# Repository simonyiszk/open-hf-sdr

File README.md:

Open HF SDR
===========

# Specs
* 0.5-30 MHz input freq range

# Receiver
## First stage
* 30 MHz low-pass filter
* Programmable auttenator with 10, 20, and 30 dB options
* Highly linear mixer to 37.224 MHz IF

## Second stage
* IF filter for 37.224 MHz
* IF amplifier
* Mixer to 9 MHz IF

## Third stage
* IF filter for 9 MHz IF with 0.5 MHz bandwidth
* Diff amp to ADC

## Fourth stage
* ADC with 8 MSps, undersampling the 9 MHz IF to 1 MHz

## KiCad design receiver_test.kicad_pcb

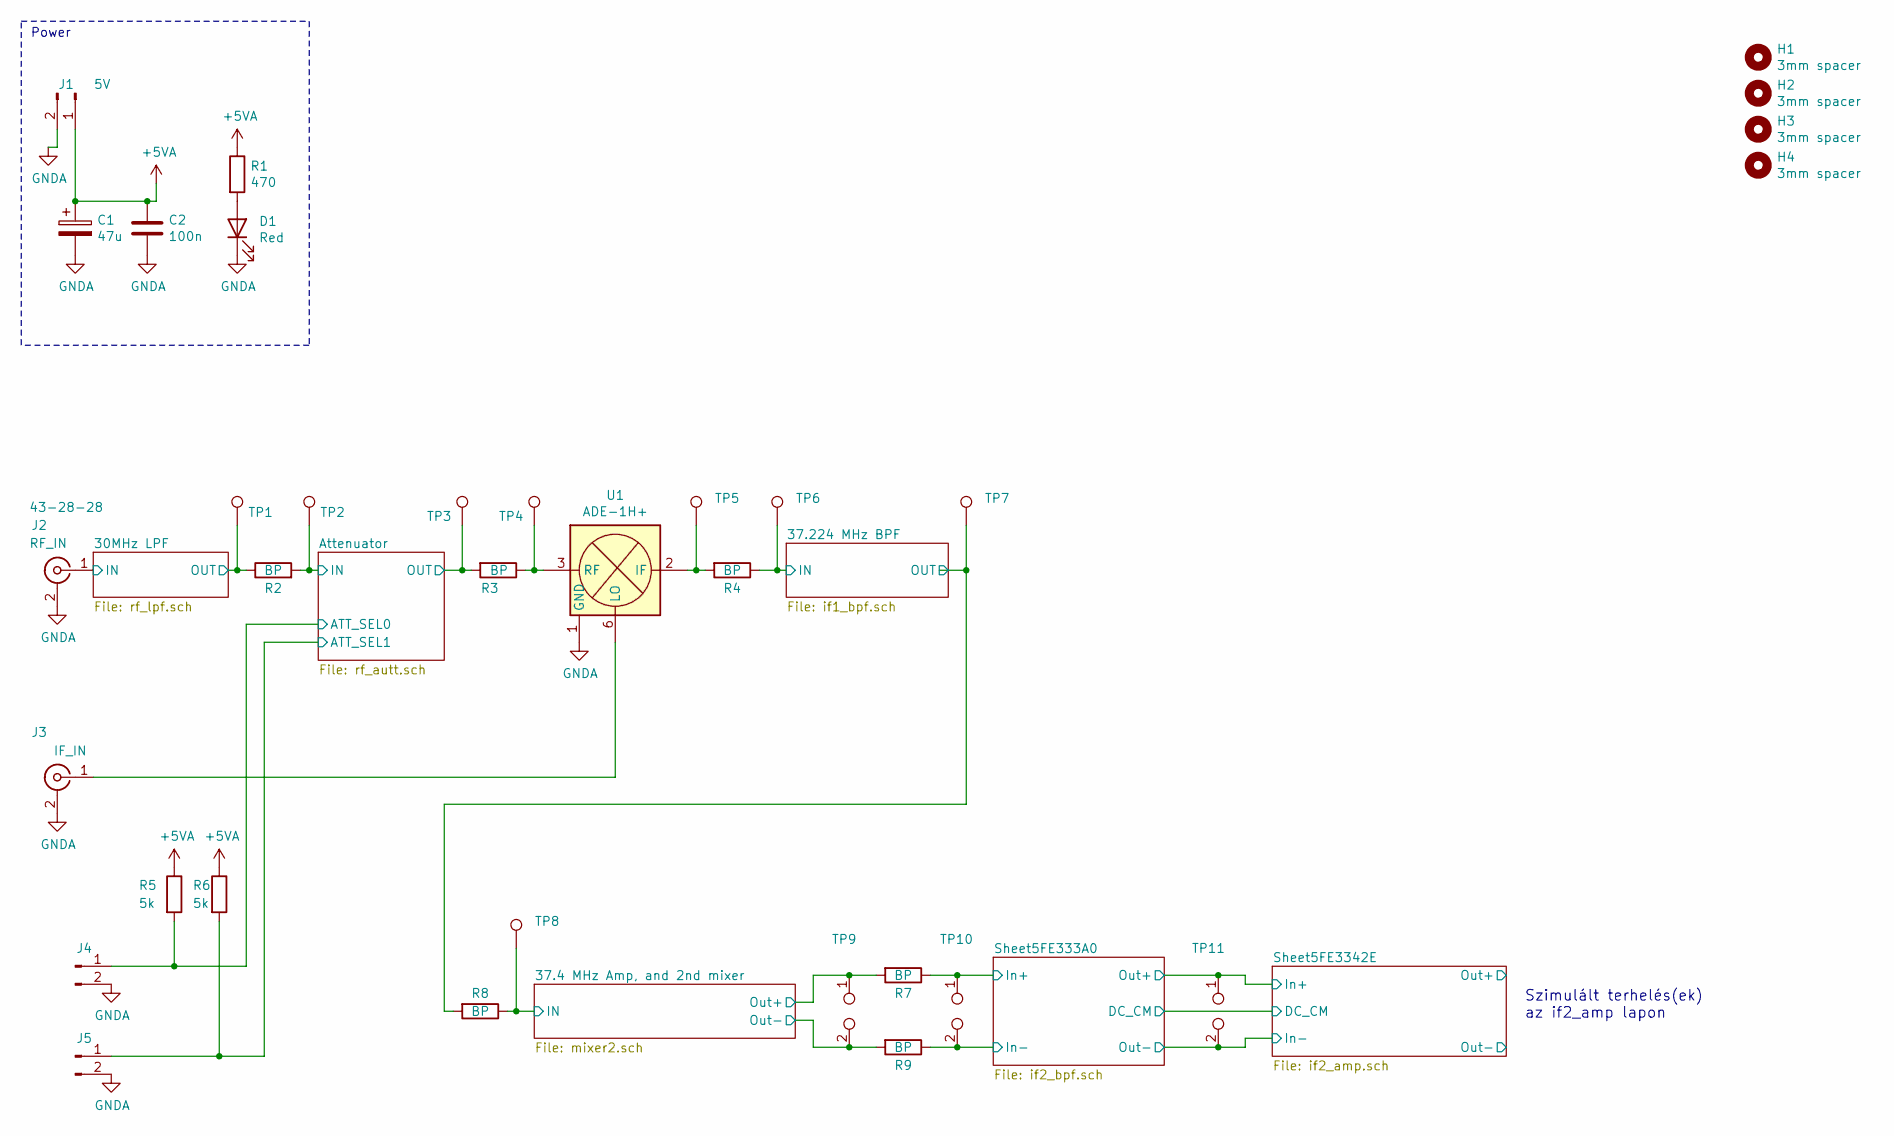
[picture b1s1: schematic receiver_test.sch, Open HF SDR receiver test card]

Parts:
C1: 47u; CP_Elec_6.3x5.3
C2: 100n; C_0805_2012Metric_Pad1.15x1.40mm_HandSolder
D1: Red; LED_0805_2012Metric_Pad1.15x1.40mm_HandSolder
H1, H2, H3, H4: 3mm spacer; MountingHole_3.2mm_M3
J1: 5V; PinSocket_1x02_P2.54mm_Vertical
J2: RF_IN; SMA_Molex_73251-1153_EdgeMount_Horizontal
J3: IF_IN; SMA_Molex_73251-1153_EdgeMount_Horizontal
J4, J5: Conn_01x02_Male; PinSocket_1x02_P2.54mm_Vertical
R1: 470; R_0805_2012Metric_Pad1.15x1.40mm_HandSolder
R2, R3, R4, R7, R8, R9: BP; R_1206_3216Metric_Pad1.42x1.75mm_HandSolder
R5, R6: 5k; R_0805_2012Metric_Pad1.15x1.40mm_HandSolder
TP1, TP2, TP3, TP4, TP5, TP6, TP7, TP8: TestPoint; PinHeader_1x01_P2.54mm_Vertical
TP9, TP10, TP11: TestPoint_2Pole; PinHeader_1x02_P2.54mm_Vertical
U1: ADE-1H+; Mini-Circuits_CD542_LandPatternPL-052

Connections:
+5VA: C1.1, C2.1, J1.1, R1.1, R5.1, R6.1; also elsewhere on the board
/30MHz LPF/IN: J2.1 (In); also elsewhere on the board
/30MHz LPF/OUT: R2.1, TP1.1; also elsewhere on the board
/37.4 MHz Amp, and 2nd mixer/IN: R8.1, TP8.1; also elsewhere on the board
/37.4 MHz Amp, and 2nd mixer/Out+: R7.2, TP9.1; also elsewhere on the board
/37.4 MHz Amp, and 2nd mixer/Out-: R9.2, TP9.2; also elsewhere on the board
/37.224 MHz BPF/IN: R4.1, TP6.1; also elsewhere on the board
/Attenuator/ATT_SEL0: J4.1, R5.2; also elsewhere on the board
/Attenuator/ATT_SEL1: J5.1, R6.2; also elsewhere on the board
/Attenuator/IN: R2.2, TP2.1; also elsewhere on the board
/Attenuator/OUT: R3.2, TP3.1; also elsewhere on the board
/Sheet5FE333A0/In+: R7.1, TP10.1; also elsewhere on the board
/Sheet5FE333A0/In-: R9.1, TP10.2; also elsewhere on the board
/Sheet5FE3342E/In+: TP11.1; also elsewhere on the board
/Sheet5FE3342E/In-: TP11.2; also elsewhere on the board
GNDA: C1.2, C2.2, D1.1 (K), J1.2, J2.2 (Ext), J3.2 (Ext), J4.2, J5.2, U1.1 (GND), U1.4 (GND), U1.5 (GND); also elsewhere on the board
unnamed: D1.2 (A), R1.2
unnamed: J3.1 (In), U1.6 (LO)
unnamed: R3.1, TP4.1, U1.3 (RF)
unnamed: R4.2, TP5.1, U1.2 (IF)
unnamed: R8.2, TP7.1

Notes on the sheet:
Power
Szimulált terhelés(ek) az if2_amp lapon

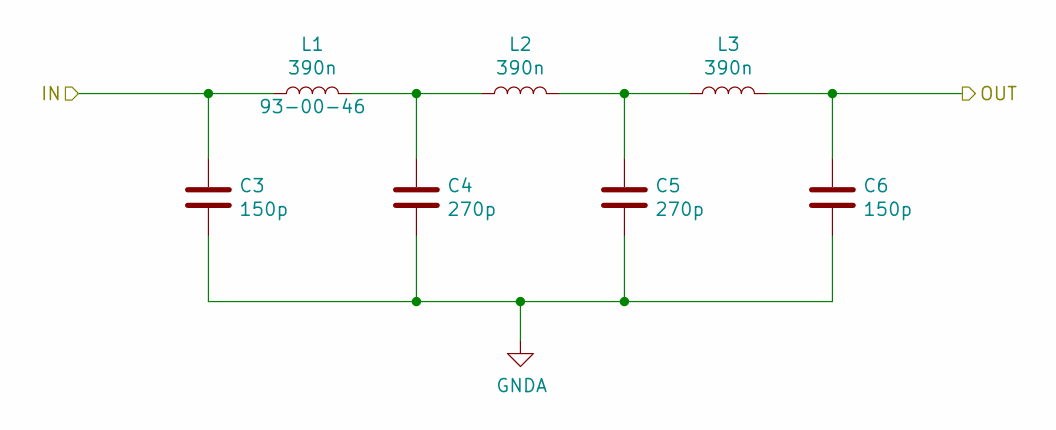
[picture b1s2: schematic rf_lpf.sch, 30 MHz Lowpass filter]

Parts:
C3, C6: 150p; C_0805_2012Metric_Pad1.15x1.40mm_HandSolder
C4, C5: 270p; C_0805_2012Metric_Pad1.15x1.40mm_HandSolder
L1, L2, L3: 390n; L_1206_3216Metric_Pad1.42x1.75mm_HandSolder

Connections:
/30MHz LPF/IN: C3.1, L1.1; also elsewhere on the board
/30MHz LPF/OUT: C6.1, L3.2; also elsewhere on the board
GNDA: C3.2, C4.2, C5.2, C6.2; also elsewhere on the board
unnamed: C4.1, L1.2, L2.1
unnamed: C5.1, L2.2, L3.1

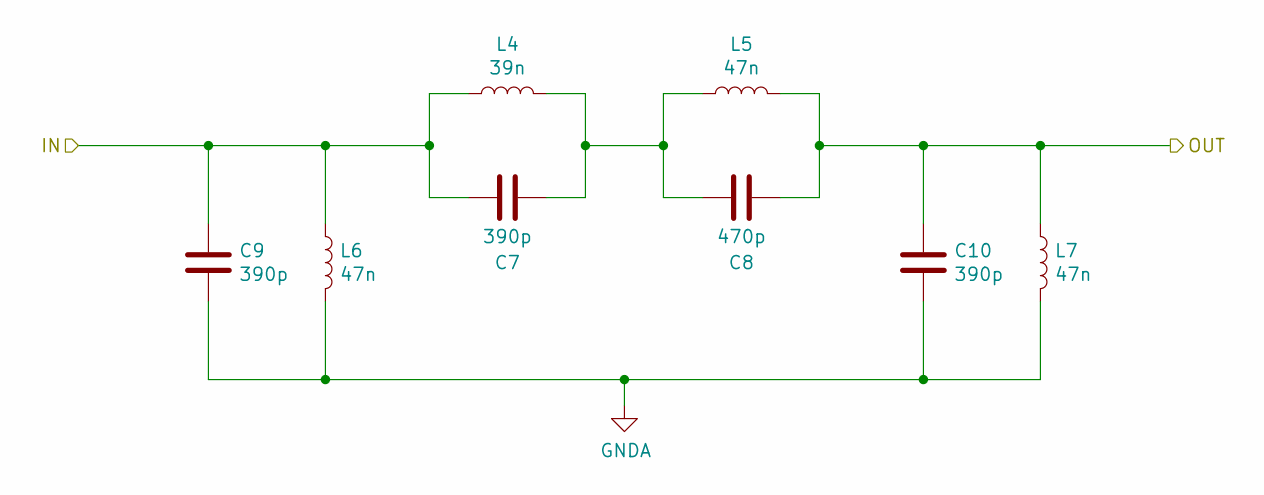
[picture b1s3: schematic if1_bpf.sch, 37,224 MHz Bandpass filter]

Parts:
C7, C9, C10: 390p; C_0805_2012Metric_Pad1.15x1.40mm_HandSolder
C8: 470p; C_0805_2012Metric_Pad1.15x1.40mm_HandSolder
L4: 39n; L_0402_1005Metric_Pad0.77x0.64mm_HandSolder; Farnell 2846682RL
L5, L6, L7: 47n; L_0603_1608Metric_Pad1.05x0.95mm_HandSolder

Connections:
/37.224 MHz BPF/IN: C7.1, C9.1, L4.1, L6.1; also elsewhere on the board
/37.224 MHz BPF/OUT: C8.2, C10.1, L5.2, L7.1
GNDA: C9.2, C10.2, L6.2, L7.2; also elsewhere on the board
unnamed: C7.2, C8.1, L4.2, L5.1

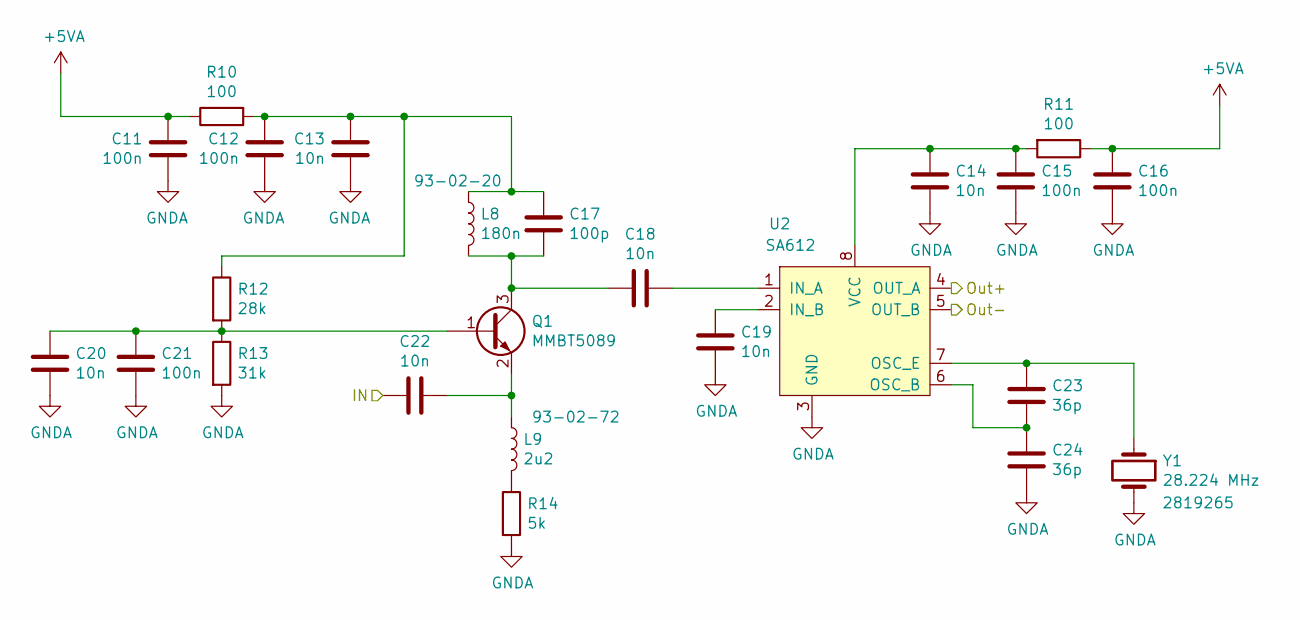
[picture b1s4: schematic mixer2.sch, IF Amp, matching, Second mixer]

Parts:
C11, C12, C15, C16, C21: 100n; C_0805_2012Metric_Pad1.15x1.40mm_HandSolder
C13, C14, C18, C19, C20, C22: 10n; C_0805_2012Metric_Pad1.15x1.40mm_HandSolder
C17: 100p; C_0805_2012Metric_Pad1.15x1.40mm_HandSolder
C23, C24: 36p; C_0805_2012Metric_Pad1.15x1.40mm_HandSolder
L8: 180n; L_1210_3225Metric_Pad1.42x2.65mm_HandSolder
L9: 2u2; L_0805_2012Metric_Pad1.15x1.40mm_HandSolder
Q1: MMBT5089; SOT-23
R10, R11: 100; R_0805_2012Metric_Pad1.15x1.40mm_HandSolder
R12: 28k; R_0805_2012Metric_Pad1.15x1.40mm_HandSolder
R13: 31k; R_0805_2012Metric_Pad1.15x1.40mm_HandSolder
R14: 5k; R_0805_2012Metric_Pad1.15x1.40mm_HandSolder
U2: SA612; SO-8_3.9x4.9mm_P1.27mm
Y1: 28.224 MHz; Crystal_HC49-U_Vertical; Farnell 2819265

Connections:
+5VA: C11.1, C16.1, R10.1, R11.1; also elsewhere on the board
/37.4 MHz Amp, and 2nd mixer/IN: C22.1; also elsewhere on the board
/37.4 MHz Amp, and 2nd mixer/Out+: U2.4 (OUT_A); also elsewhere on the board
/37.4 MHz Amp, and 2nd mixer/Out-: U2.5 (OUT_B); also elsewhere on the board
GNDA: C11.2, C12.2, C13.2, C14.2, C15.2, C16.2, C19.2, C20.2, C21.2, C24.2, R13.2, R14.2, U2.3 (GND), Y1.2; also elsewhere on the board
unnamed: C12.1, C13.1, C17.1, L8.1, R10.2, R12.1
unnamed: C14.1, C15.1, R11.2, U2.8 (VCC)
unnamed: C17.2, C18.2, L8.2, Q1.3 (C)
unnamed: C18.1, U2.1 (IN_A)
unnamed: C19.1, U2.2 (IN_B)
unnamed: C20.1, C21.1, Q1.1 (B), R12.2, R13.1
unnamed: C22.2, L9.1, Q1.2 (E)
unnamed: C23.1, U2.7 (OSC_E), Y1.1
unnamed: C23.2, C24.1, U2.6 (OSC_B)
unnamed: L9.2, R14.1

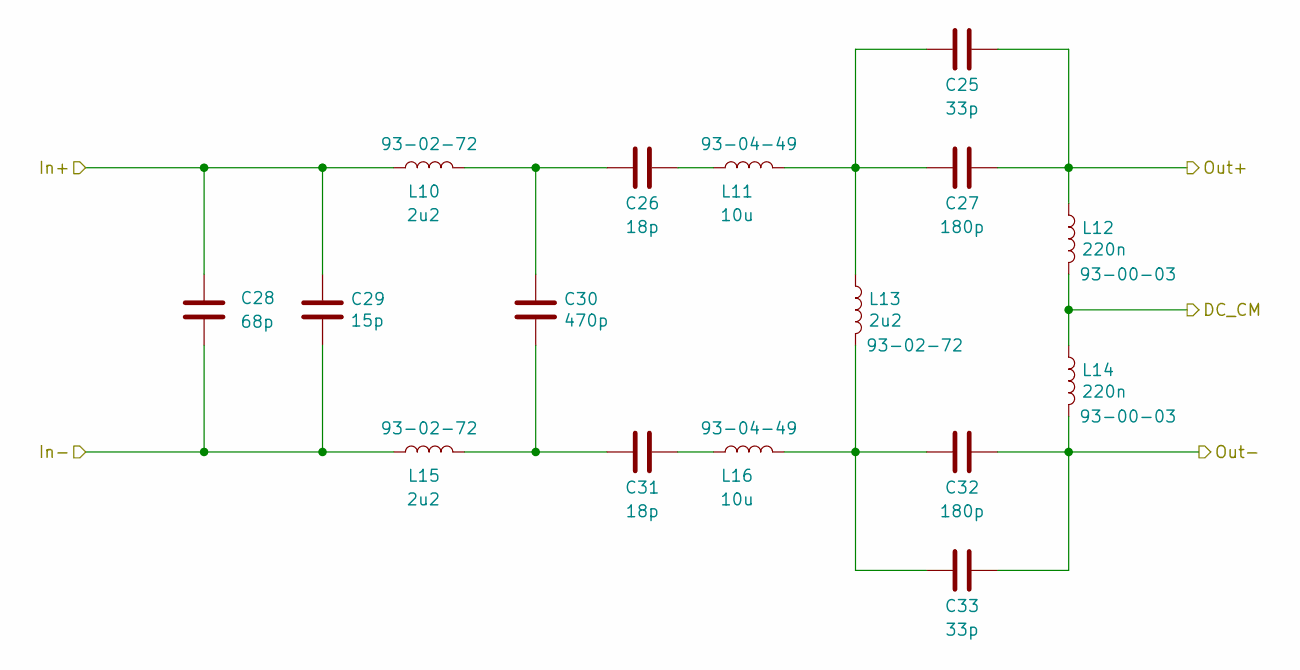
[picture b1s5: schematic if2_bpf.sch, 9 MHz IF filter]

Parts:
C25, C33: 33p; C_0805_2012Metric_Pad1.15x1.40mm_HandSolder
C26, C31: 18p; C_0805_2012Metric_Pad1.15x1.40mm_HandSolder
C27, C32: 180p; C_0805_2012Metric_Pad1.15x1.40mm_HandSolder
C28: 68p; C_0805_2012Metric_Pad1.15x1.40mm_HandSolder
C29: 15p; C_0805_2012Metric_Pad1.15x1.40mm_HandSolder
C30: 470p; C_0805_2012Metric_Pad1.15x1.40mm_HandSolder
L10, L13, L15: 2u2; L_0805_2012Metric_Pad1.15x1.40mm_HandSolder
L11, L16: 10u; L_1210_3225Metric_Pad1.42x2.65mm_HandSolder
L12, L14: 220n; L_1210_3225Metric_Pad1.42x2.65mm_HandSolder

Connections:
/Sheet5FE333A0/DC_CM: L12.2, L14.1; also elsewhere on the board
/Sheet5FE333A0/In+: C28.1, C29.1, L10.1; also elsewhere on the board
/Sheet5FE333A0/In-: C28.2, C29.2, L15.1; also elsewhere on the board
/Sheet5FE3342E/In+: C25.1, C27.1, L12.1; also elsewhere on the board
/Sheet5FE3342E/In-: C32.2, C33.2, L14.2; also elsewhere on the board
unnamed: C25.2, C27.2, L11.2, L13.1
unnamed: C26.1, L11.1
unnamed: C26.2, C30.1, L10.2
unnamed: C30.2, C31.2, L15.2
unnamed: C31.1, L16.1
unnamed: C32.1, C33.1, L13.2, L16.2

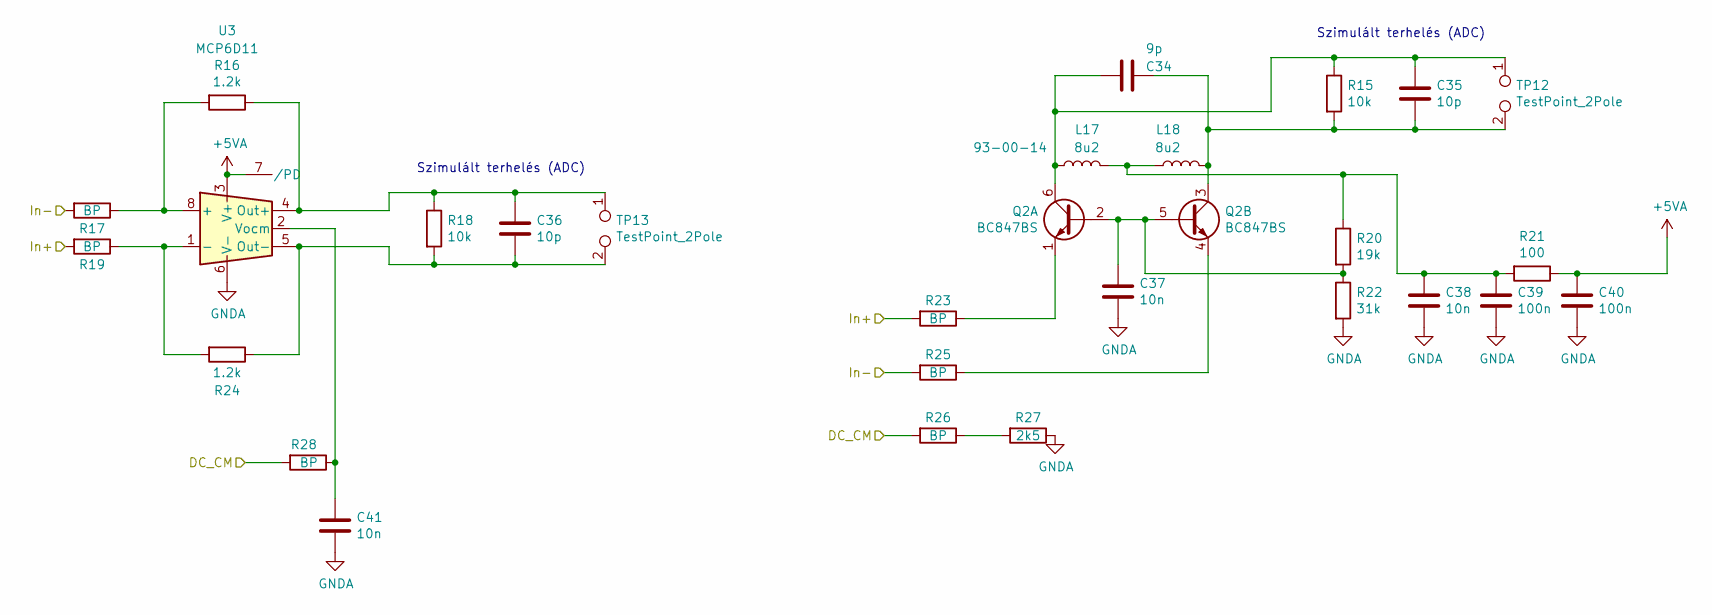
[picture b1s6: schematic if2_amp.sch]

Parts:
C34: 9p; C_0805_2012Metric_Pad1.15x1.40mm_HandSolder
C35, C36: 10p; C_0805_2012Metric_Pad1.15x1.40mm_HandSolder
C37, C38, C41: 10n; C_0805_2012Metric_Pad1.15x1.40mm_HandSolder
C39, C40: 100n; C_0805_2012Metric_Pad1.15x1.40mm_HandSolder
L17, L18: 8u2; L_1210_3225Metric_Pad1.42x2.65mm_HandSolder
Q2: BC847BS; SOT-363_SC-70-6
R15, R18: 10k; R_0805_2012Metric_Pad1.15x1.40mm_HandSolder
R16, R24: 1.2k; R_0805_2012Metric_Pad1.15x1.40mm_HandSolder
R17, R19, R23, R25, R26, R28: BP; R_1206_3216Metric_Pad1.42x1.75mm_HandSolder
R20: 19k; R_0805_2012Metric_Pad1.15x1.40mm_HandSolder
R21: 100; R_0805_2012Metric_Pad1.15x1.40mm_HandSolder
R22: 31k; R_0805_2012Metric_Pad1.15x1.40mm_HandSolder
R27: 2k5; R_0805_2012Metric_Pad1.15x1.40mm_HandSolder
TP12, TP13: TestPoint_2Pole; PinHeader_1x02_P2.54mm_Vertical
U3: MCP6D11; MSOP-8_3x3mm_P0.65mm

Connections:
+5VA: C40.1, R21.1, U3.3 (V+), U3.7 (/PD); also elsewhere on the board
/Sheet5FE333A0/DC_CM: R26.2, R28.2; also elsewhere on the board
/Sheet5FE3342E/In+: R19.2, R23.2; also elsewhere on the board
/Sheet5FE3342E/In-: R17.2, R25.2; also elsewhere on the board
GNDA: C37.2, C38.2, C39.2, C40.2, C41.2, R22.2, R27.1, U3.6 (V-); also elsewhere on the board
unnamed: C34.1, C35.2, L18.2, Q2.3 (C2), R15.2, TP12.2
unnamed: C34.2, C35.1, L17.1, Q2.6 (C1), R15.1, TP12.1
unnamed: C36.1, R16.1, R18.1, TP13.1, U3.4 (Out+)
unnamed: C36.2, R18.2, R24.1, TP13.2, U3.5 (Out-)
unnamed: C37.1, Q2.2 (B1), Q2.5 (B2), R20.2, R22.1
unnamed: C38.1, C39.1, L17.2, L18.1, R20.1, R21.2
unnamed: C41.1, R28.1, U3.2 (Vocm)
unnamed: Q2.1 (E1), R23.1
unnamed: Q2.4 (E2), R25.1
unnamed: R16.2, R17.1, U3.8 (+)
unnamed: R19.1, R24.2, U3.1 (-)
unnamed: R26.1, R27.2

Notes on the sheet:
Szimulált terhelés (ADC)

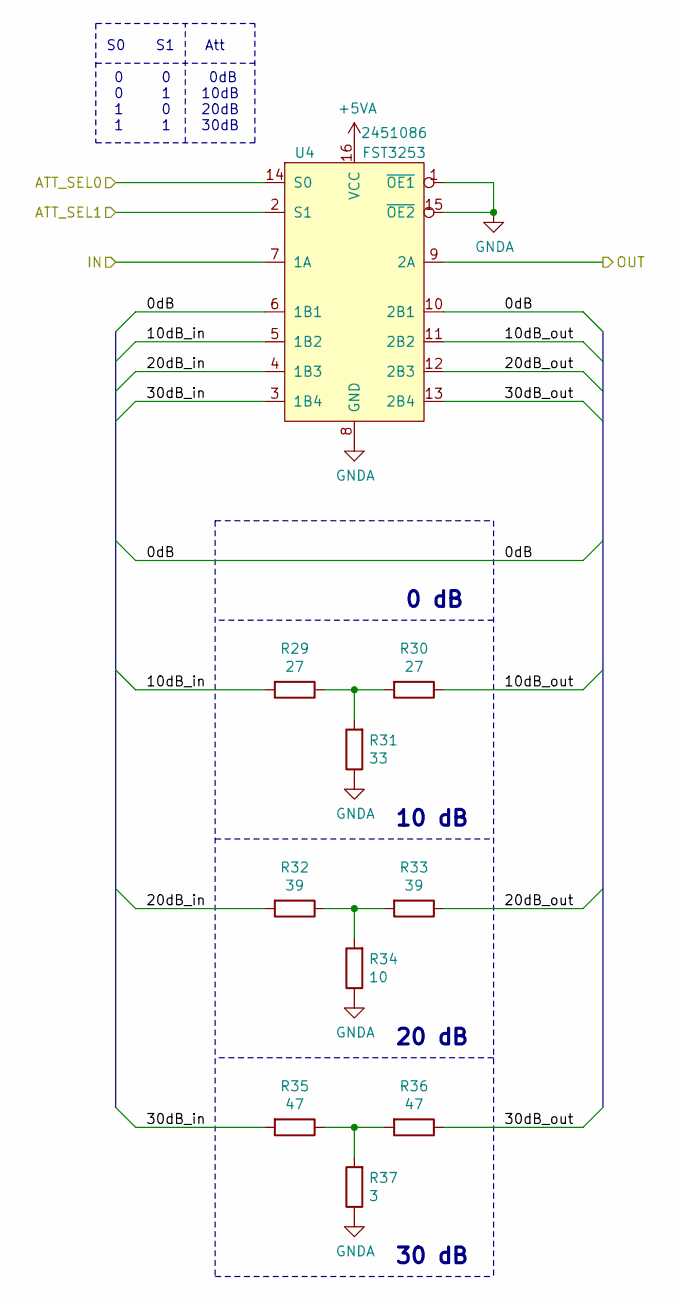
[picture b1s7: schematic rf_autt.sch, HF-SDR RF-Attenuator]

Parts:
R29, R30: 27; R_0805_2012Metric_Pad1.15x1.40mm_HandSolder
R31: 33; R_0805_2012Metric_Pad1.15x1.40mm_HandSolder
R32, R33: 39; R_0805_2012Metric_Pad1.15x1.40mm_HandSolder
R34: 10; R_0805_2012Metric_Pad1.15x1.40mm_HandSolder
R35, R36: 47; R_0805_2012Metric_Pad1.15x1.40mm_HandSolder
R37: 3; R_0805_2012Metric_Pad1.15x1.40mm_HandSolder
U4: FST3253; TSSOP-16_4.4x5mm_P0.65mm; Farnell 2451086

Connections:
+5VA: U4.16 (VCC); also elsewhere on the board
/Attenuator/0dB: U4.6 (1B1), U4.10 (2B1)
/Attenuator/10dB_in: R29.2, U4.5 (1B2)
/Attenuator/10dB_out: R30.1, U4.11 (2B2)
/Attenuator/20dB_in: R32.2, U4.4 (1B3)
/Attenuator/20dB_out: R33.1, U4.12 (2B3)
/Attenuator/30dB_in: R35.2, U4.3 (1B4)
/Attenuator/30dB_out: R36.1, U4.13 (2B4)
/Attenuator/ATT_SEL0: U4.14 (S0); also elsewhere on the board
/Attenuator/ATT_SEL1: U4.2 (S1); also elsewhere on the board
/Attenuator/IN: U4.7 (1A); also elsewhere on the board
/Attenuator/OUT: U4.9 (2A); also elsewhere on the board
GNDA: R31.1, R34.1, R37.1, U4.1 (~OE1), U4.8 (GND), U4.15 (~OE2); also elsewhere on the board
unnamed: R29.1, R30.2, R31.2
unnamed: R32.1, R33.2, R34.2
unnamed: R35.1, R36.2, R37.2

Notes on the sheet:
30 dB
20 dB
10 dB
0 dB
S0 S1 Att 0 0 0dB 0 1 10dB 1 0 20dB 1 1 30dB

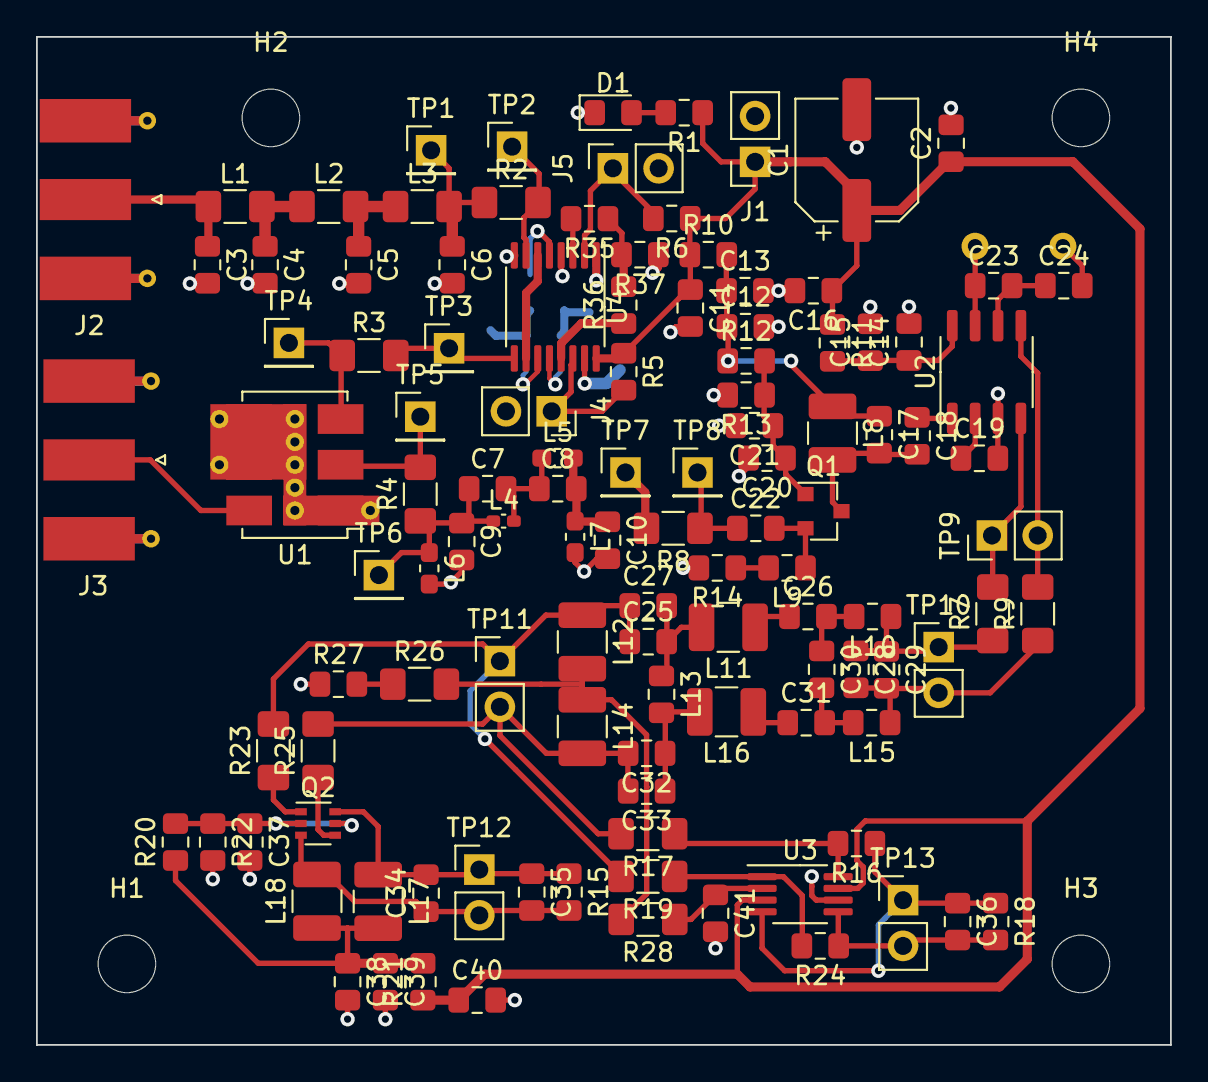
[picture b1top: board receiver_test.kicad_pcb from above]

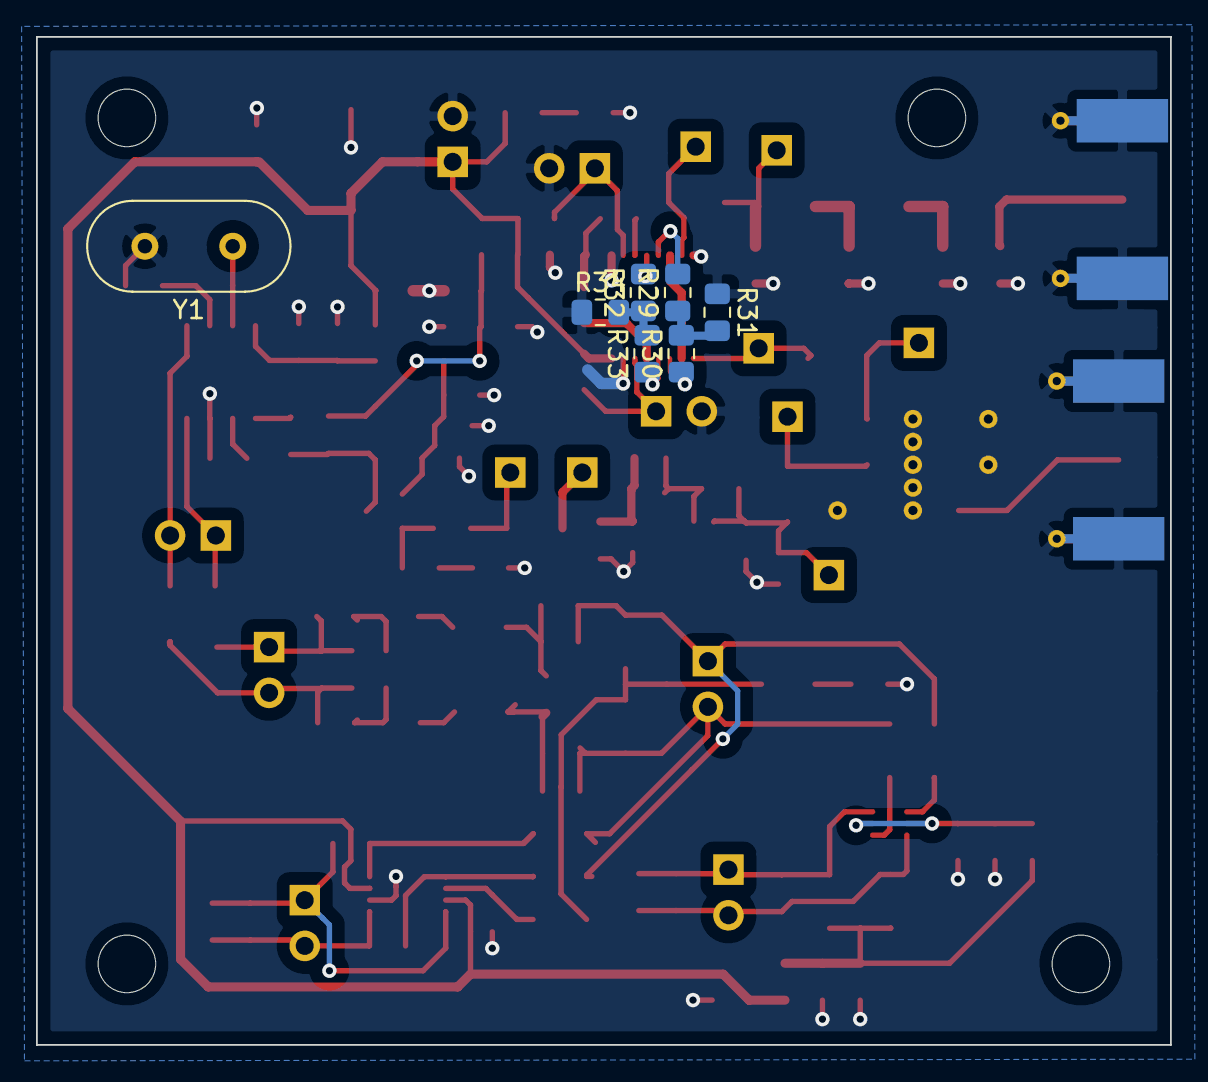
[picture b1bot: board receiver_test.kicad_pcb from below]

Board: 2 copper layers, 63.0 x 56.0 mm, 126 parts (7 on the bottom side), 64 nets.

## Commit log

2020-12-20 English readme receiver draft
2020-12-23 SDR receiver blocks
2020-12-23 RF filter implemented
2020-12-23 Attenuator
2020-12-24 Attenuator revised
2020-12-24 Second mixer
2020-12-26 37.4Mega
2020-12-26 Block diagram arrangement
2020-12-26 attenuator doc
2020-12-26 37.4 MHz Butterworth BPF
2020-12-26 2nd IF amp test values
2020-12-27 IF1 BPF updated
2020-12-27 Readme update to new IF
2020-12-28 if2_amp.sch
    if2_amp almost done
2020-12-28 if2_amp updated
2020-12-28 IF2 Filter Impedance Calculator
2020-12-28 if2 completed
2020-12-29 IF2 amp discrete demo
2020-12-29 IF2 AMP modified collector tank
2020-12-30 If2 50 ohm filter
2020-12-30 If2 filter ltspice file added
2020-12-31 CB diff amp LTSpice file added
2021-01-04 Tx initial commit
2021-01-08 Fix grounding in rf autt
2021-01-08 Initalize receiver test circuit
2021-01-09 Nyáktervezésre majdnem kész
2021-01-15 Receiver test panel ++
2021-01-15 IF2 filter and amp recalculate
2021-01-16 majdnem kész a nyák béta verziója
2021-01-16 if2amp BP resistor added
2021-01-16 Add part number to auttenator
2021-01-16 FPGA added
2021-01-16 if2_bpf revised + Schematic cleanup
2021-01-16 Footprint reassociation, pcb clear
2021-01-16 Pcb vHA8KDA
2021-01-16 Pcb edges and spacer part number
2021-01-17 IF1 modified to 37,224 MHz
2021-01-17 diffamp common mode fix
2021-01-17 FPGA change and new project file
2021-01-17 FPGA supply notes
2021-01-18 PCB is Done... Needs DRC check
2021-01-18 RX PCB revision: Diff amp + Mixer2
2021-01-18 Via stitching removed + Edge Cut resized
2021-01-18 RX PCB gerbers exported
2021-01-26 PSU init
2021-01-30 Nézd meg!
2021-01-31 Power supplies
2021-02-12 Add vivado project from ha1flx
2021-02-20 Vivado gitignore
2021-02-20 fpga receiver implemented
2021-02-20 finish up power supply
2021-02-26 update buck converter diodes
2021-02-26 add power on sequencing for fpga
2021-02-26 one less transistor is enough
2021-04-24 SDR-FPGA Interface v0
2021-04-24 Add notes to sdr.sch
2021-04-29 Begin the implementation of Human in-out, a few small changes
2021-05-10 add more buttons
2021-05-10 Progress in programmer sheet
2021-05-11 Add USB-FPGA bus labels
2021-05-11 Finish LED branches on programmer sheet
2021-05-12 connect leds to fpga
2021-05-12 Add USB connector
2021-05-12 plus 2 leds
2021-05-12 Add oscillator
2021-05-12 Fix power pins
2021-05-12 Add unconnected marks
2021-05-12 Connect USB buses to the FPGA
2021-05-12 Add LED15 and LED16
2021-05-12 Power supply ,,typo" fixes
2021-05-14 Center main sheet
2021-05-14 Power suppley fixes
2021-05-14 Add battery monitoring, and reverse polarity check
2021-05-14 Battery overdischarge jumper changed
2021-05-18 fix battery protection jumper
